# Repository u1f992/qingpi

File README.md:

# Qingpi

Qingpi aka NeoCtrlMod is a project for externally controlling the Nintendo 3DS.

- PCB, FPC, firmware, Python library and example application included.
- Small enough to fit in a original housing.
- Buttons, slide pad, and touch screen supported.
  - IR not yet supported, but connected (contributions welcome).
- Aim to be fully documented.

Currently FPC is provided only for 3DS XL.

## Origin of the name

Qing Pi (青皮) is a herbal remedy made from the peel of unripe citrus fruits. It is named after [Citra](https://citra-emu.org/), the famous 3DS emulator, and "Citra" is derived from "CTR", the model number of 3DS series.

## Disclaimer

This is an unofficial project and the author assumes no responsibility for any 3DS hardware modifications. Use at your own risk and discretion.

## Acknowledgments

- [3DS controller mod](https://3dscapture.com/controller/) by loopy
- [3xtDS](https://github.com/dekuNukem/3xtDS) by dekuNukem
- [Nu Hanafudaya](https://kokagem.sakura.ne.jp/font/hanafudaya/) font by さゆぬ

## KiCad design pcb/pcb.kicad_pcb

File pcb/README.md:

# PCB

## JLCPCB order

### PCB

<dl>
<dt>PCB Thickness</dt><dd>1.0</dd>
<dt>Remove Order Number</dt><dd>Specify a location</dd>
<dt>PCB Remark</dt><dd>Holes in the four corners are for position calibration. NPTH&F.Mask&F.Paste, drill holes in both the PCB and the stencil.</dd>
</dl>

### PCBA

<dl>
<dt>PCBA Type</dt><dd>Economic</dd>
<dt>Confirm Parts Placement</dt><dd>Yes</dd>
</dl>

### Stencil

<dl>
<dt>Customized size</dt><dd>Yes 50*85mm</dd>
<dt>Stencil Side</dt><dd>Top</dd>
<dt>Confirm Production file</dt><dd>Yes</dd>
<dt>Stencil Remark</dt><dd>Holes in the four corners are for position calibration. NPTH&F.Mask&F.Paste, drill holes in both the PCB and the stencil.</dd>
</dl>

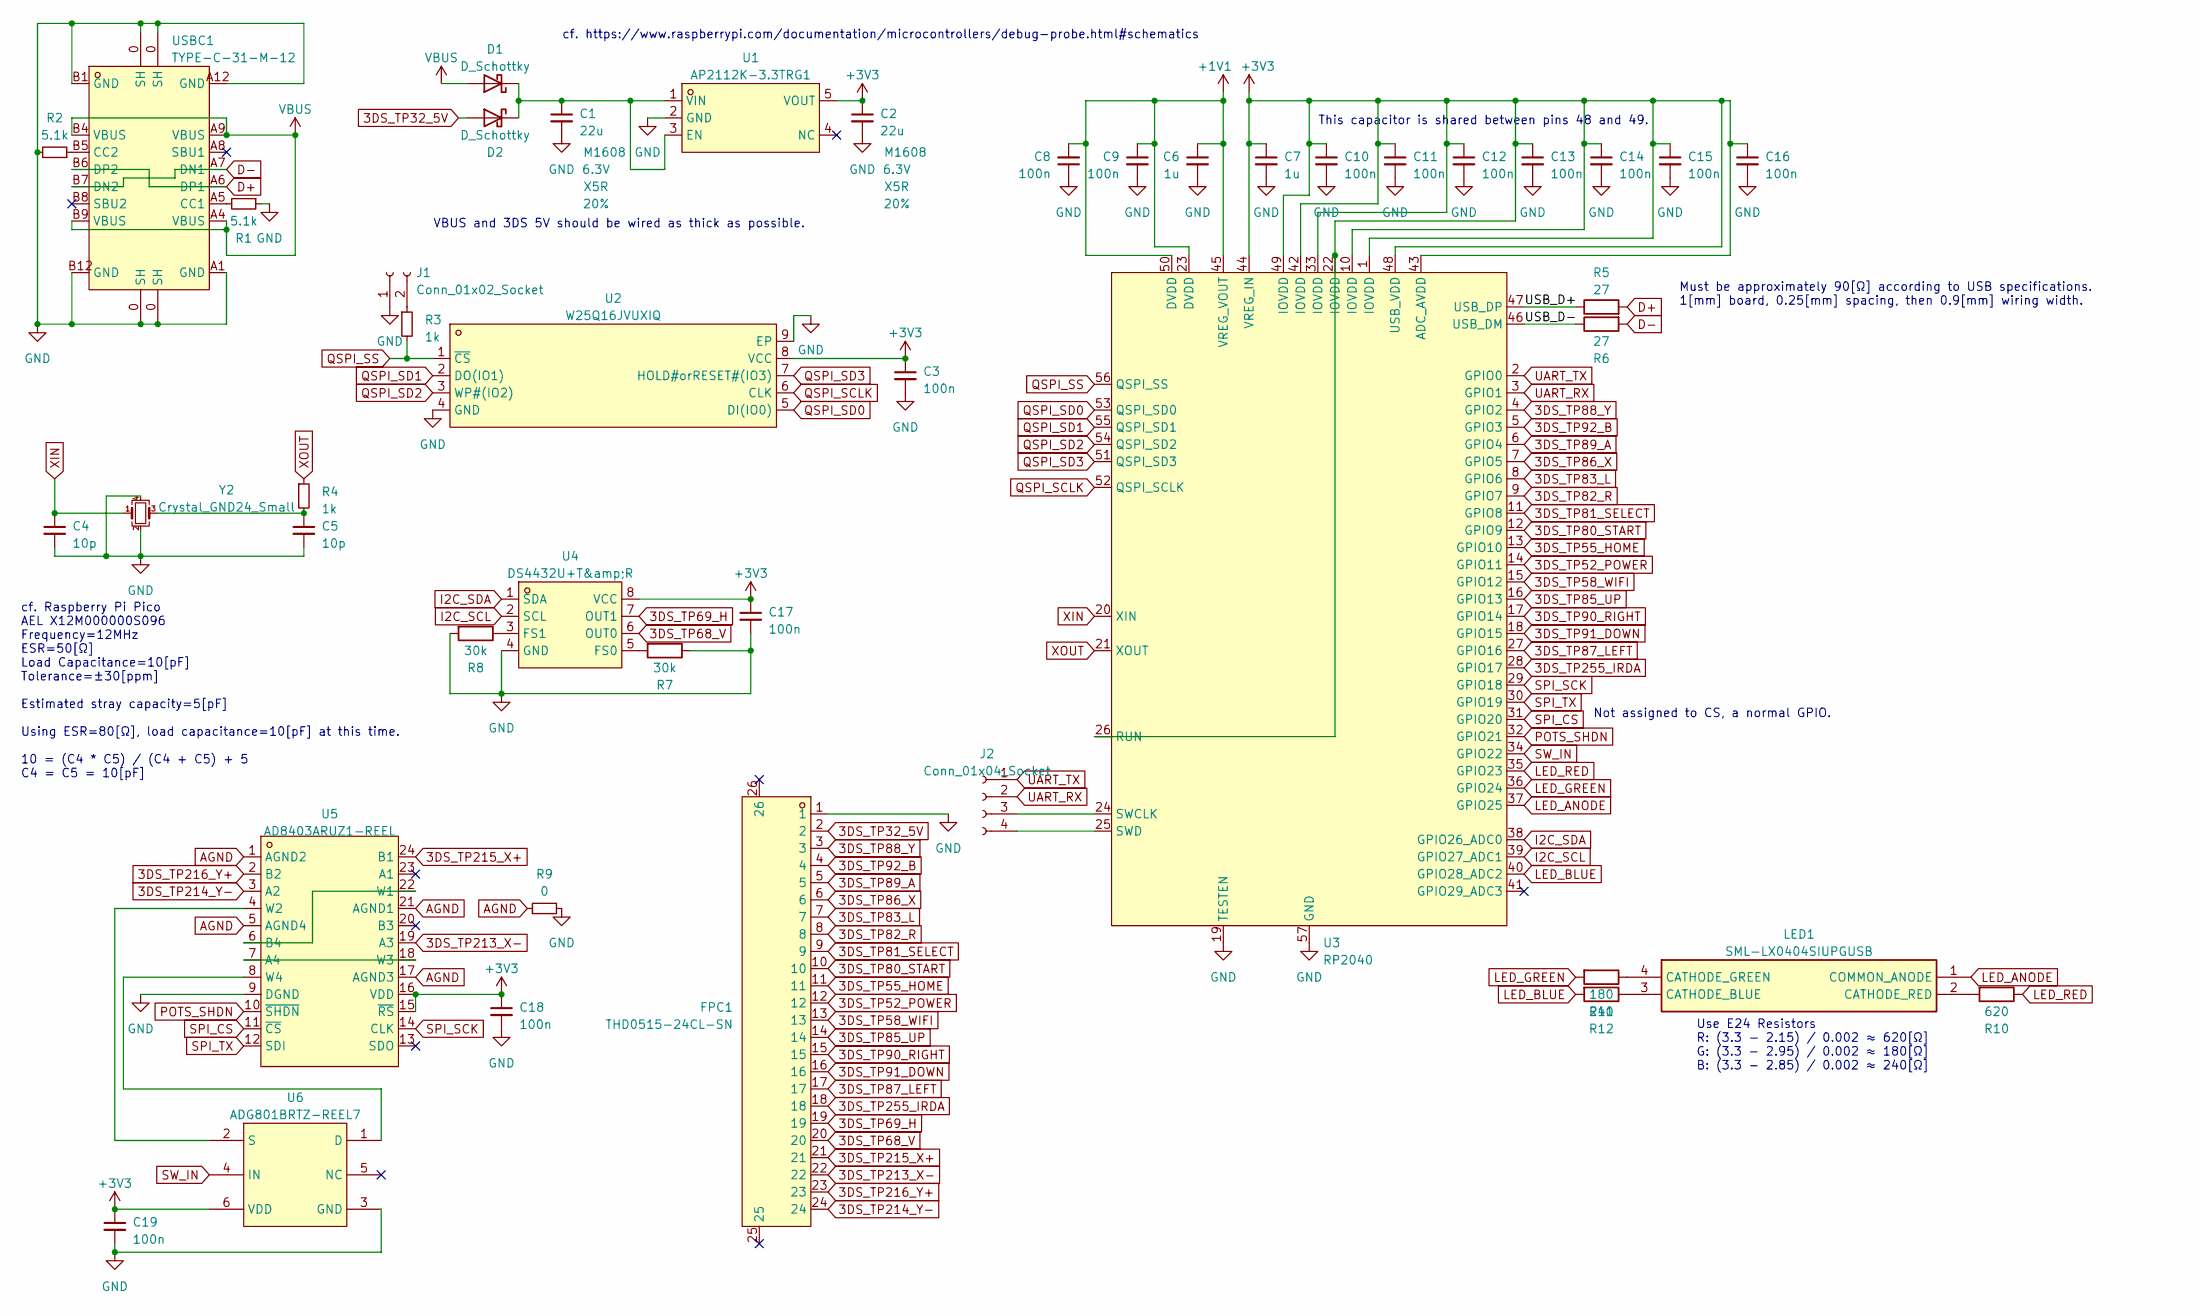
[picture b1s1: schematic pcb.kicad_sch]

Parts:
C1, C2: 22u; C_0603_1608Metric; LCSC C3015158
C3, C8, C9, C10, C11, C12, C13, C14, C15, C16, C17, C18, C19: 100n; C_0402_1005Metric
C4, C5: 10p; C_0402_1005Metric
C6, C7: 1u; C_0402_1005Metric
D1, D2: D_Schottky; D_SOD-523; LCSC C99683
FPC1: THD0515-24CL-SN; FPC-SMD_24P-P0.50_THD0515-24CL-SN; LCSC Part C283150
J1: Conn_01x02_Socket; PinSocket_1x02_P2.54mm_Vertical
J2: Conn_01x04_Socket; PinSocket_1x04_P2.54mm_Vertical
LED1: SML-LX0404SIUPGUSB; Manufacturer_Part_Number SML-LX0404SIUPGUSB; Mouser Part Number 696-LX0404SIUPGUSB
R1, R2: 5.1k; R_0402_1005Metric
R3, R4: 1k; R_0402_1005Metric
R5, R6: 27; R_0402_1005Metric
R7, R8: 30k; R_0402_1005Metric
R9: 0; R_0402_1005Metric
R10: 620; R_0402_1005Metric
R11: 180; R_0402_1005Metric
R12: 240; R_0402_1005Metric
U1: AP2112K-3.3TRG1; SOT-25-5_L2.9-W1.6-P0.95-LS2.8-BL; LCSC Part C51118
U2: W25Q16JVUXIQ; USON-8_L3.0-W2.0-P0.50-BL-EP; LCSC Part C2843335
U3: RP2040; LQFN-56_L7.0-W7.0-P0.4-EP; LCSC Part C2040
U4: DS4432U+T&amp;R; UMAX-8_L3.0-W3.0-P0.65-LS4.9-BL; LCSC Part C2679620
U5: AD8403ARUZ1-REEL; TSSOP-24_L7.8-W4.4-P0.65-LS6.4-BL; LCSC Part C652783
U6: ADG801BRTZ-REEL7; SOT-23-6_L2.9-W1.6-P0.95-LS2.8-BL; LCSC Part C208016
USBC1: TYPE-C-31-M-12; USB-C_SMD-TYPE-C-31-M-12; LCSC Part C165948
Y2: Crystal_GND24_Small; Crystal_SMD_3225-4Pin_3.2x2.5mm; LCSC C9002

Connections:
3DS_TP32_5V: D2.2 (A), FPC1.2
3DS_TP52_POWER: FPC1.12, U3.14 (GPIO11)
3DS_TP55_HOME: FPC1.11, U3.13 (GPIO10)
3DS_TP58_WIFI: FPC1.13, U3.15 (GPIO12)
3DS_TP68_V: FPC1.20, U4.6 (OUT0)
3DS_TP69_H: FPC1.19, U4.7 (OUT1)
3DS_TP80_START: FPC1.10, U3.12 (GPIO9)
3DS_TP81_SELECT: FPC1.9, U3.11 (GPIO8)
3DS_TP82_R: FPC1.8, U3.9 (GPIO7)
3DS_TP83_L: FPC1.7, U3.8 (GPIO6)
3DS_TP85_UP: FPC1.14, U3.16 (GPIO13)
3DS_TP86_X: FPC1.6, U3.7 (GPIO5)
3DS_TP87_LEFT: FPC1.17, U3.27 (GPIO16)
3DS_TP88_Y: FPC1.3, U3.4 (GPIO2)
3DS_TP89_A: FPC1.5, U3.6 (GPIO4)
3DS_TP90_RIGHT: FPC1.15, U3.17 (GPIO14)
3DS_TP91_DOWN: FPC1.16, U3.18 (GPIO15)
3DS_TP92_B: FPC1.4, U3.5 (GPIO3)
3DS_TP213_X-: FPC1.22, U5.19 (A3)
3DS_TP214_Y-: FPC1.24, U5.3 (A2)
3DS_TP215_X+: FPC1.21, U5.24 (B1)
3DS_TP216_Y+: FPC1.23, U5.2 (B2)
3DS_TP255_IRDA: FPC1.18, U3.28 (GPIO17)
+1V1: C6.1, C8.2, C9.1, U3.23 (DVDD), U3.45 (VREG_VOUT), U3.50 (DVDD)
+3V3: C2.1, C3.1, C7.1, C10.1, C11.1, C12.1, C13.1, C14.1, C15.1, C16.1, C17.1, C18.1, C19.1, U1.5 (VOUT), U2.8 (VCC), U3.1 (IOVDD), U3.10 (IOVDD), U3.22 (IOVDD), U3.26 (RUN), U3.33 (IOVDD), U3.42 (IOVDD), U3.43 (ADC_AVDD), U3.44 (VREG_IN), U3.48 (USB_VDD), U3.49 (IOVDD), U4.8 (VCC), U5.15 (~RS), U5.16 (VDD), U6.6 (VDD)
/USB_D+: R5.1, U3.47 (USB_DP)
/USB_D-: R6.1, U3.46 (USB_DM)
AGND: R9.1, U5.1 (AGND2), U5.5 (AGND4), U5.17 (AGND3), U5.21 (AGND1)
D+: R5.2, USBC1.A6 (DP1), USBC1.B6 (DP2)
D-: R6.2, USBC1.A7 (DN1), USBC1.B7 (DN2)
GND: C1.2, C2.2, C3.2, C4.2, C5.2, C6.2, C7.2, C8.1, C9.2, C10.2, C11.2, C12.2, C13.2, C14.2, C15.2, C16.2, C17.2, C18.2, C19.2, FPC1.1, J1.1, R1.1, R2.2, R7.1, R8.2, R9.2, U1.2 (GND), U2.4 (GND), U2.9 (EP), U3.19 (TESTEN), U3.57 (GND), U4.4 (GND), U5.9 (DGND), U6.3 (GND), USBC1.0 (SH), USBC1.A1 (GND), USBC1.A12 (GND), USBC1.B1 (GND), USBC1.B12 (GND), Y2.2, Y2.4
I2C_SCL: U3.39 (GPIO27_ADC1), U4.2 (SCL)
I2C_SDA: U3.38 (GPIO26_ADC0), U4.1 (SDA)
LED_ANODE: LED1.1 (COMMON_ANODE), U3.37 (GPIO25)
LED_BLUE: R12.2, U3.40 (GPIO28_ADC2)
LED_GREEN: R11.2, U3.36 (GPIO24)
LED_RED: R10.1, U3.35 (GPIO23)
unnamed: C5.1, R4.2, Y2.3
unnamed: C1.1, D1.1 (K), D2.1 (K), U1.1 (VIN), U1.3 (EN)
unnamed: J1.2, R3.1
unnamed: J2.3, U3.24 (SWCLK)
unnamed: J2.4, U3.25 (SWD)
unnamed: LED1.3 (CATHODE_BLUE), R12.1
unnamed: LED1.4 (CATHODE_GREEN), R11.1
unnamed: LED1.2 (CATHODE_RED), R10.2
unnamed: R7.2, U4.5 (FS0)
unnamed: R8.1, U4.3 (FS1)
unnamed: U5.7 (A4), U5.18 (W3)
unnamed: U5.6 (B4), U5.22 (W1)
unnamed: U5.4 (W2), U6.2 (S)
unnamed: U5.8 (W4), U6.1 (D)
unnamed: R1.2, USBC1.A5 (CC1)
unnamed: R2.1, USBC1.B5 (CC2)
POTS_SHDN: U3.32 (GPIO21), U5.10 (~SHDN)
QSPI_SCLK: U2.6 (CLK), U3.52 (QSPI_SCLK)
QSPI_SD0: U2.5 (DI(IO0)), U3.53 (QSPI_SD0)
QSPI_SD1: U2.2 (DO(IO1)), U3.55 (QSPI_SD1)
QSPI_SD2: U2.3 (WP#(IO2)), U3.54 (QSPI_SD2)
QSPI_SD3: U2.7 (HOLD#orRESET#(IO3)), U3.51 (QSPI_SD3)
QSPI_SS: R3.2, U2.1 (~CS), U3.56 (QSPI_SS)
SPI_CS: U3.31 (GPIO20), U5.11 (~CS)
SPI_SCK: U3.29 (GPIO18), U5.14 (CLK)
SPI_TX: U3.30 (GPIO19), U5.12 (SDI)
SW_IN: U3.34 (GPIO22), U6.4 (IN)
UART_RX: J2.2, U3.3 (GPIO1)
UART_TX: J2.1, U3.2 (GPIO0)
VBUS: D1.2 (A), USBC1.A4 (VBUS), USBC1.A9 (VBUS), USBC1.B4 (VBUS), USBC1.B9 (VBUS)
XIN: C4.1, U3.20 (XIN), Y2.1
XOUT: R4.1, U3.21 (XOUT)

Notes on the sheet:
Not assigned to CS, a normal GPIO.
Must be approximately 90[Ω] according to USB specifications. 1[mm] board, 0.25[mm] spacing, then 0.9[mm] wiring width.
cf. Raspberry Pi Pico AEL X12M000000S096 Frequency=12MHz ESR=50[Ω] Load Capacitance=10[pF] Tolerance=±30[ppm] Estimated stray capacity=5[pF] Using ESR=80[Ω], load capacitance=10[pF] at this time. 10 = (C4 * C5) / (C4 + C5) + 5 C4 = C5 = 10[pF]
Use E24 Resistors R: (3.3 - 2.15) / 0.002 ≈ 620[Ω] G: (3.3 - 2.95) / 0.002 ≈ 180[Ω] B: (3.3 - 2.85) / 0.002 ≈ 240[Ω]
cf. https://www.raspberrypi.com/documentation/microcontrollers/debug-probe.html#schematics
VBUS and 3DS 5V should be wired as thick as possible.
This capacitor is shared between pins 48 and 49.

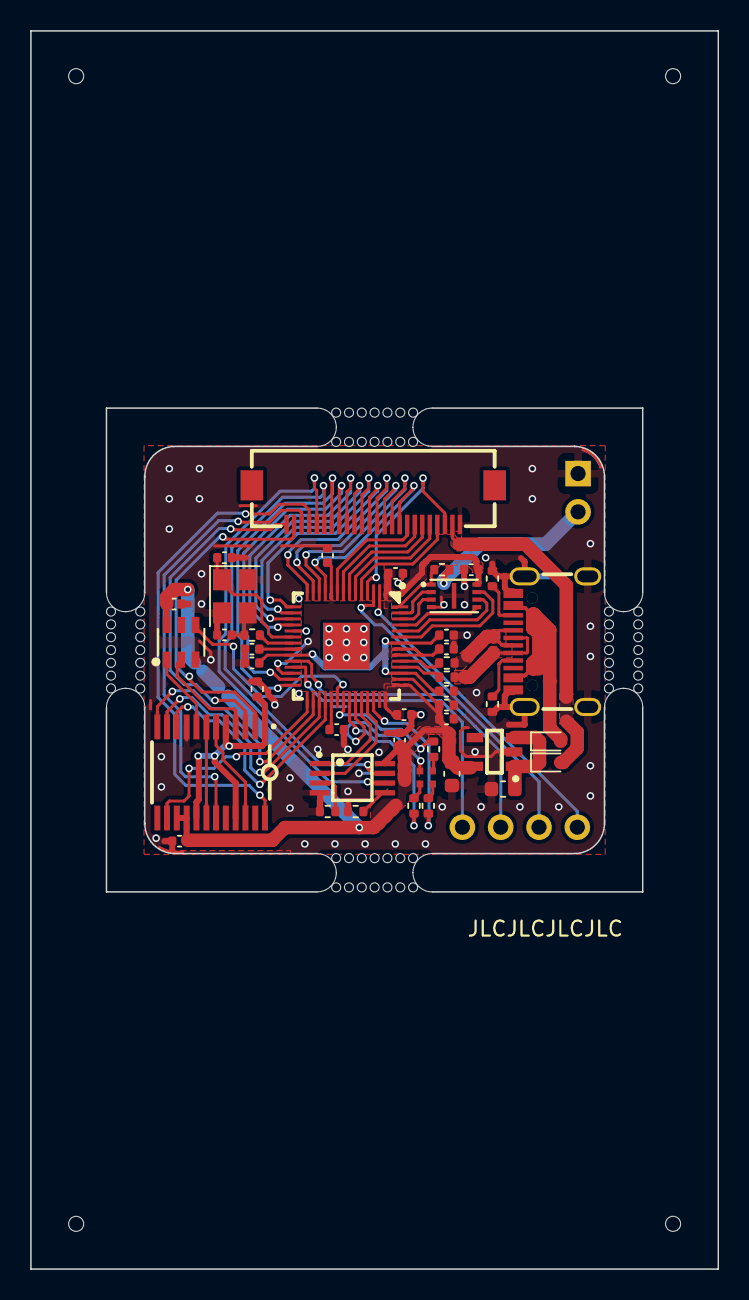
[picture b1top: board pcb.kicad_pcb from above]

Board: 2 copper layers, 45.6 x 82.1 mm, 45 parts (0 on the bottom side), 69 nets.

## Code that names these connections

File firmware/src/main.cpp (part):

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static const pin_size_t PIN_R = 15;
static const pin_size_t PIN_L = 16;
// static const pin_size_t PIN_IRDA = 17;
static const pin_size_t PIN_SPI_SCK = 18;
static const pin_size_t PIN_SPI_TX = 19;
static const pin_size_t PIN_SPI_CS = 20;
static const pin_size_t PIN_POTS_SHDN = 21;
static const pin_size_t PIN_SW_IN = 22;
static const pin_size_t PIN_LED_RED = 23;
static const pin_size_t PIN_LED_GREEN = 24;
static const pin_size_t PIN_LED_ANODE = 25;
static const pin_size_t PIN_I2C_SDA = 26;
static const pin_size_t PIN_I2C_SCL = 27;
static const pin_size_t PIN_LED_BLUE = 28;

static const uint16_t TOUCHSCREEN_X_MAX = 320;
static const uint8_t TOUCHSCREEN_Y_MAX = 240;
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    hat_left = qpi_button_new((QpiGeneralPurposeIOInterface *)gpio_left);
    hat = qpi_hat_new(hat_up, hat_right, hat_down, hat_left);

    Wire1.setSDA(PIN_I2C_SDA);
    Wire1.setSCL(PIN_I2C_SCL);
    Wire1.begin();
    dac = ds4432_new(&Wire1);
    dac_v = ds4432_adapter_new(dac, DS4432_OUT0);
    dac_h = ds4432_adapter_new(dac, DS4432_OUT1);
    sp = qpi_slidepad_new((QpiCurrentDAConverterInterface *)dac_v, (QpiCurrentDAConverterInterface *)dac_h);

    SPI.setSCK(PIN_SPI_SCK);
    SPI.setTX(PIN_SPI_TX);
    // SPI.setCS(PIN_SPI_CS);
    pinMode(PIN_SPI_CS, OUTPUT); // PIN_SPI_CS is not assigned to CS, but a normal GPIO.
    digitalWrite(PIN_SPI_CS, HIGH);
    SPI.begin();
    pinMode(PIN_POTS_SHDN, OUTPUT);
    digitalWrite(PIN_POTS_SHDN, LOW);
    pots = ad840x_new(&SPI, PIN_SPI_CS, PIN_POTS_SHDN);
    pots_v = ad840x_adapter_new(pots, AD840X_RDAC2);
    pots_h = ad840x_triple_adapter_new(pots, AD840X_RDAC3, AD840X_RDAC1, AD840X_RDAC4);
    pinMode(PIN_SW_IN, OUTPUT);
    sw = adg801_new(PIN_SW_IN);
    sw_adapter = adg801_adapter_new(sw);
    ts = qpi_touchscreen_new((QpiDigitalPotentiometerInterface *)pots_v, (QpiDigitalPotentiometerInterface *)pots_h, (QpiSPSTSwitchInterface *)sw_adapter);

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        buffer != NULL);

    analogWriteResolution(ANALOG_WRITE_RESOLUTION);
    pinMode(PIN_LED_ANODE, OUTPUT_8MA);
    digitalWrite(PIN_LED_ANODE, LOW);
    anode = sml_lx0404siupgusb_arduino_digital_adapter_new(PIN_LED_ANODE);
    pinMode(PIN_LED_RED, OUTPUT);
    digitalWrite(PIN_LED_RED, HIGH);
    pwm_red = sml_lx0404siupgusb_arduino_analog_adapter_new(PIN_LED_RED, ANALOG_WRITE_RESOLUTION);
    pinMode(PIN_LED_GREEN, OUTPUT);
    digitalWrite(PIN_LED_GREEN, HIGH);
    pwm_green = sml_lx0404siupgusb_arduino_analog_adapter_new(PIN_LED_GREEN, ANALOG_WRITE_RESOLUTION);
    pinMode(PIN_LED_BLUE, OUTPUT);
    digitalWrite(PIN_LED_BLUE, HIGH);
    pwm_blue = sml_lx0404siupgusb_arduino_analog_adapter_new(PIN_LED_BLUE, ANALOG_WRITE_RESOLUTION);
    led = sml_lx0404siupgusb_new((SML_LX0404SIUPGUSBDigitalOutputInterface *)anode,
                                 (SML_LX0404SIUPGUSBAnalogOutputInterface *)pwm_red,
                                 (SML_LX0404SIUPGUSBAnalogOutputInterface *)pwm_green,
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
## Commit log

2023-05-06 Add README.md
2023-05-06 Create LICENSE
2023-05-06 Add pictures
2023-05-07 Add flex project
2023-05-07 Add touch screen diagram
2023-05-14 Extend flex to touch screen
2023-06-11 Update plot
2023-06-11 Add firmware project
2023-06-16 Update devcontainer
2023-06-18 Edit firmware
2023-06-18 Add loop states
2023-07-02 Update firmware
2023-08-06 Improve touchscreen
2023-08-13 Slidepad
2023-08-15 Isolate *.h to lib
2023-08-15 Change pins
2023-08-20 Add PCB
2023-08-20 Update PCB
2023-09-10 Add fpc
2023-09-24 Change pin assign
2023-09-24 Update documents
2023-09-24 Change repository name
2023-09-26 Split core functionality into the library
2023-09-26 Change naming conventions for components
2023-10-27 Update gitignore in pcb
2023-10-27 Stash old pcb
2023-10-28 Change pots to use
2023-10-29 Add setup script
2023-11-02 Add flex footprint
2023-11-03 flex
2023-11-04 Order ready
2023-11-04 Slight adjustment of GND wiring
2023-11-05 Update README.md, change project name.
2023-11-05 Add logo
2023-11-05 Add silkscreen of logo on PCB
2023-11-05 Change name
2023-11-05 Adjust text
2023-11-06 Rename flex project
2023-11-06 Change footprint name
2023-11-08 Create Makefile
2023-11-08 Run potrace on Windows
2023-11-09 Add Python library
2023-11-09 Recreate tools with Poetry
2023-11-10 Add NeoCtrlMod application
2023-11-11 Adjust 3D model position
2023-11-11 Add image on README.md
2023-11-12 Improve test
2023-11-14 Add new headers
2023-11-14 Add nxamf submodule
2023-11-15 Adapter should not adjust init state
2023-11-15 Pin assign
2023-11-16 Add class diagram for firmware
2023-11-16 Update diagram
2023-11-17 Remove old files
2023-11-18 Type-C connector stick out as much as possible
2023-11-18 Add fastener
2023-11-27 Update flex order detail
2023-11-27 Adjust FPC connector slightly to the left
2023-11-27 Change pictures
2023-11-27 Add GND via
2023-11-27 Tweak BOOTSEL path
2023-11-27 Add URL on silkscreen
2023-11-27 Make the text a little bigger
2023-12-02 Add SML-LX0404SIUPGUSB
2023-12-02 Update schematic
2023-12-02 For production
2023-12-02 Update pictures
2023-12-11 Tweak holes
2023-12-13 Resize
2023-12-17 Fix incorrect mapping
2023-12-20 Add SML-LX0404SIUPGUSB library
2023-12-20 Update ctinypalette
2023-12-20 Add LED
2023-12-20 Change LED color according to type of operation
2023-12-22 Change logo
2023-12-22 Remove .gitattributes
2023-12-23 Rename Python library
2023-12-23 Update build script
2023-12-23 Update tools
2023-12-23 Update PCB image
2023-12-23 Add images
2023-12-25 Upload qingpi-python to PyPI
2023-12-25 Change Python version
2023-12-26 Fix README.md
2023-12-26 Change Python version requirement
2023-12-26 Expose init function
2023-12-29 qingpictrl app
2024-01-10 Update qingpi-python
2024-01-12 Add prefix to file names
2024-01-12 Update image
2025-12-10 Remove submodules and add libraries as regular directories
